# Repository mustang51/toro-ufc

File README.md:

# toro-ufc

USB Up Front Controller, attempting to represent multiple cockpits (F/A-18, F-16, F-15E, A-10C, AV-8B...)

It comprises:

* 12 button numerical pad.
* 10 button in both left and right vertical pads.
* 7 button in horizontal pad.
* 2 rotary encoders with push.
* 2 big buttons.
* 2 small buttons.
* 4 rockers (up/down).
* 2 triple position lever-switches, one with safety cover.
* 4 way dobber lever.
* 6 analog axis (4 lateral, 2 frontal).

## Pin assignments and key matrix

[Pin assignments](doc/pin_assignments.md)

## Bill of materials

* Around 400 grams of PLA for 3D printing.

* 1 STM32F103C6T6 microcontroller.

* 4 ordered PCBs.

* 31 cherry mx switches.

* 2 KY-040 rotary encoders.

* 6 regular 100k potentiometers.

* 12 microswitches.

* 2 MTS-103 ON-OFF-ON lever switches.

* 2 19 mm momentary pushbuttons.

* 12 JST XH 6 pin male PCB connectors.

* 4 JST XH 10 pin male PCB connectors.

* 2 JST XH 8 pin male PCB connectors.

* 1 JST XH 4 pin male PCB connector.

* 44 SMD 0805 diodes.

* 1 JST XH 6 pin 10 mm dual headed cable.

* 1 JST XH 6 pin 20 mm dual headed cable.

* 1 JST XH 8 pin 10 mm dual headed cable.

* 1 JST XH 10 pin 10 mm dual headed cable.

* 8 JST XH 6 pin 20 mm single headed cable.

* 2 JST XJ 10 pin 20 mm single headed cable.

* 1 JST XH 4 pin 20 mm single headed cable.

* 1 mini-USB breakout board.

## Progress pictures

First releases.

Front panel.

Keyswitches PCBs mounted.

First versions of keycaps.

Detail of some PCBs.

[Video of working first prototype.](https://photos.app.goo.gl/QciC3gtiZSFWSCfe9)

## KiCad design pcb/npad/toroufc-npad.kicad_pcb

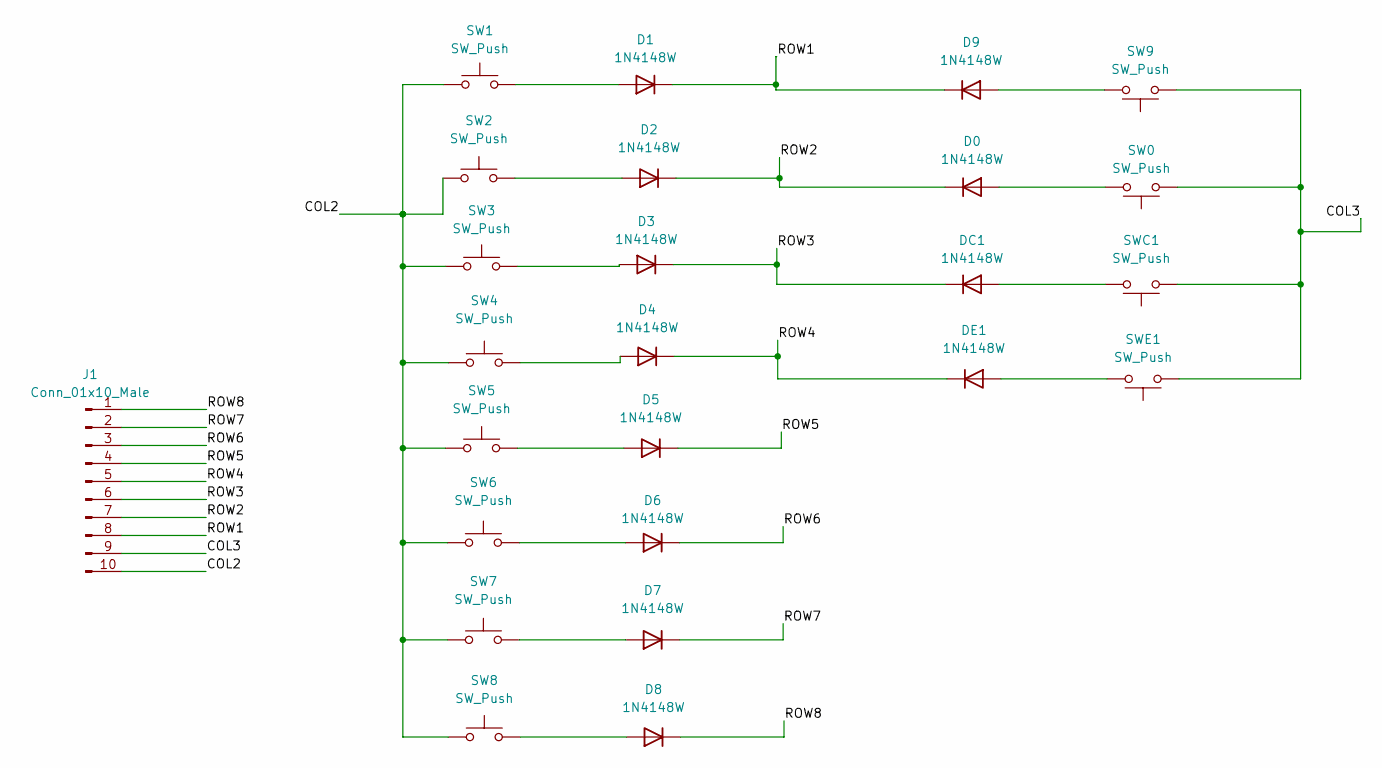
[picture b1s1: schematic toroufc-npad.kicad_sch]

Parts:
D0, D1, D2, D3, D4, D5, D6, D7, D8, D9: 1N4148W; D_SOD-123
DC1: 1N4148W; D_SOD-123
DE1: 1N4148W; D_SOD-123
J1: Conn_01x10_Male; JST_XH_B10B-XH-AM_1x10_P2.50mm_Vertical
SW0, SW1, SW2, SW3, SW4, SW5, SW6, SW7, SW8, SW9: SW_Push; SW_Cherry_MX_PCB
SWC1: SW_Push; SW_Cherry_MX_PCB
SWE1: SW_Push; SW_Cherry_MX_PCB

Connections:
/COL2: J1.10, SW1.1, SW2.1, SW3.1, SW4.1, SW5.1, SW6.1, SW7.1, SW8.1
/COL3: J1.9, SW0.1, SW9.1, SWC1.1, SWE1.1
/ROW1: D1.1 (K), D9.1 (K), J1.8
/ROW2: D0.1 (K), D2.1 (K), J1.7
/ROW3: D3.1 (K), DC1.1 (K), J1.6
/ROW4: D4.1 (K), DE1.1 (K), J1.5
/ROW5: D5.1 (K), J1.4
/ROW6: D6.1 (K), J1.3
/ROW7: D7.1 (K), J1.2
/ROW8: D8.1 (K), J1.1
unnamed: D0.2 (A), SW0.2
unnamed: D1.2 (A), SW1.2
unnamed: D2.2 (A), SW2.2
unnamed: D3.2 (A), SW3.2
unnamed: D4.2 (A), SW4.2
unnamed: D5.2 (A), SW5.2
unnamed: D6.2 (A), SW6.2
unnamed: D7.2 (A), SW7.2
unnamed: D8.2 (A), SW8.2
unnamed: D9.2 (A), SW9.2
unnamed: DC1.2 (A), SWC1.2
unnamed: DE1.2 (A), SWE1.2

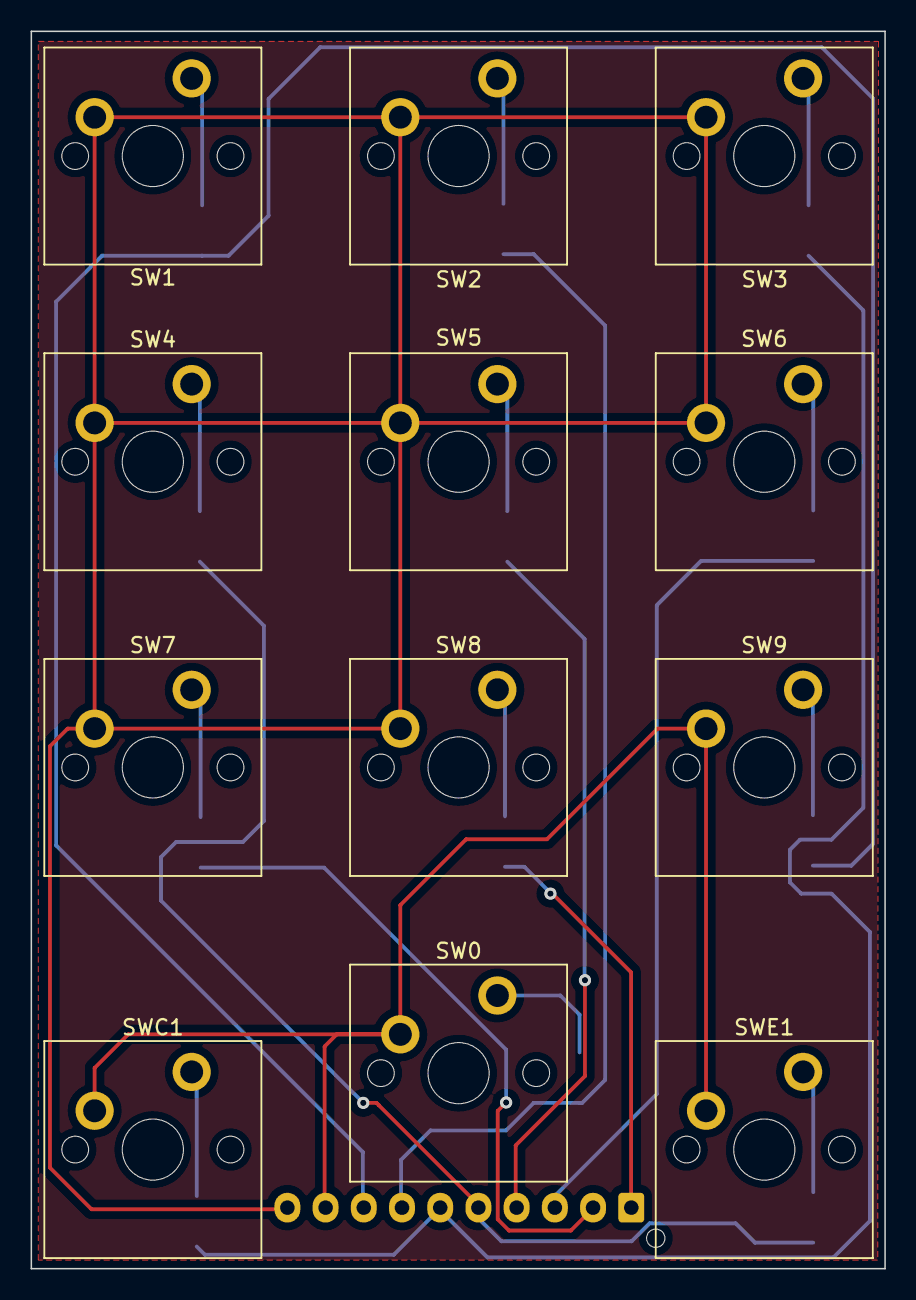
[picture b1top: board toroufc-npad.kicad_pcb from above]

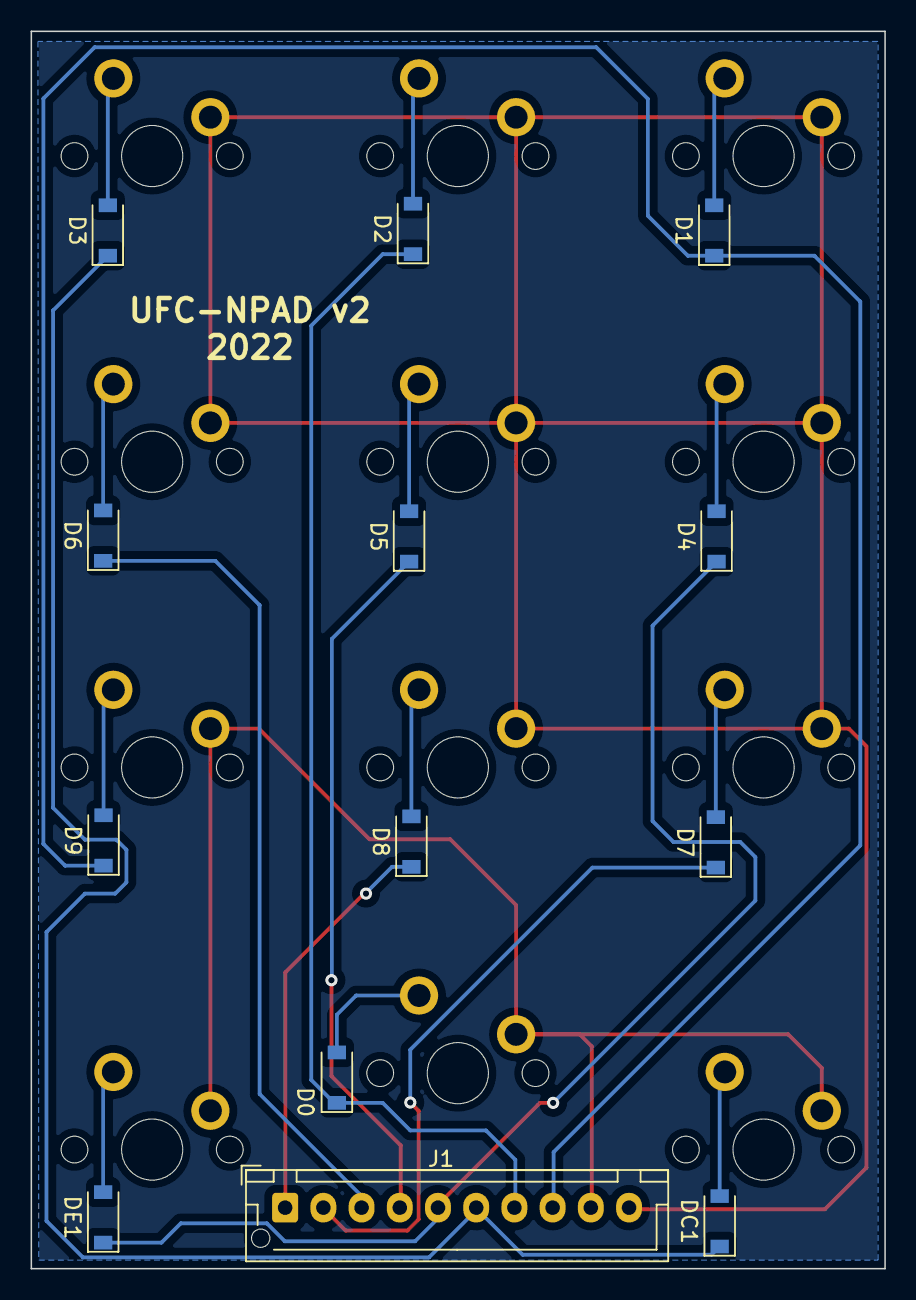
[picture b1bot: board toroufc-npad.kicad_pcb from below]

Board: 2 copper layers, 55.9 x 80.9 mm, 25 parts (13 on the bottom side), 22 nets.

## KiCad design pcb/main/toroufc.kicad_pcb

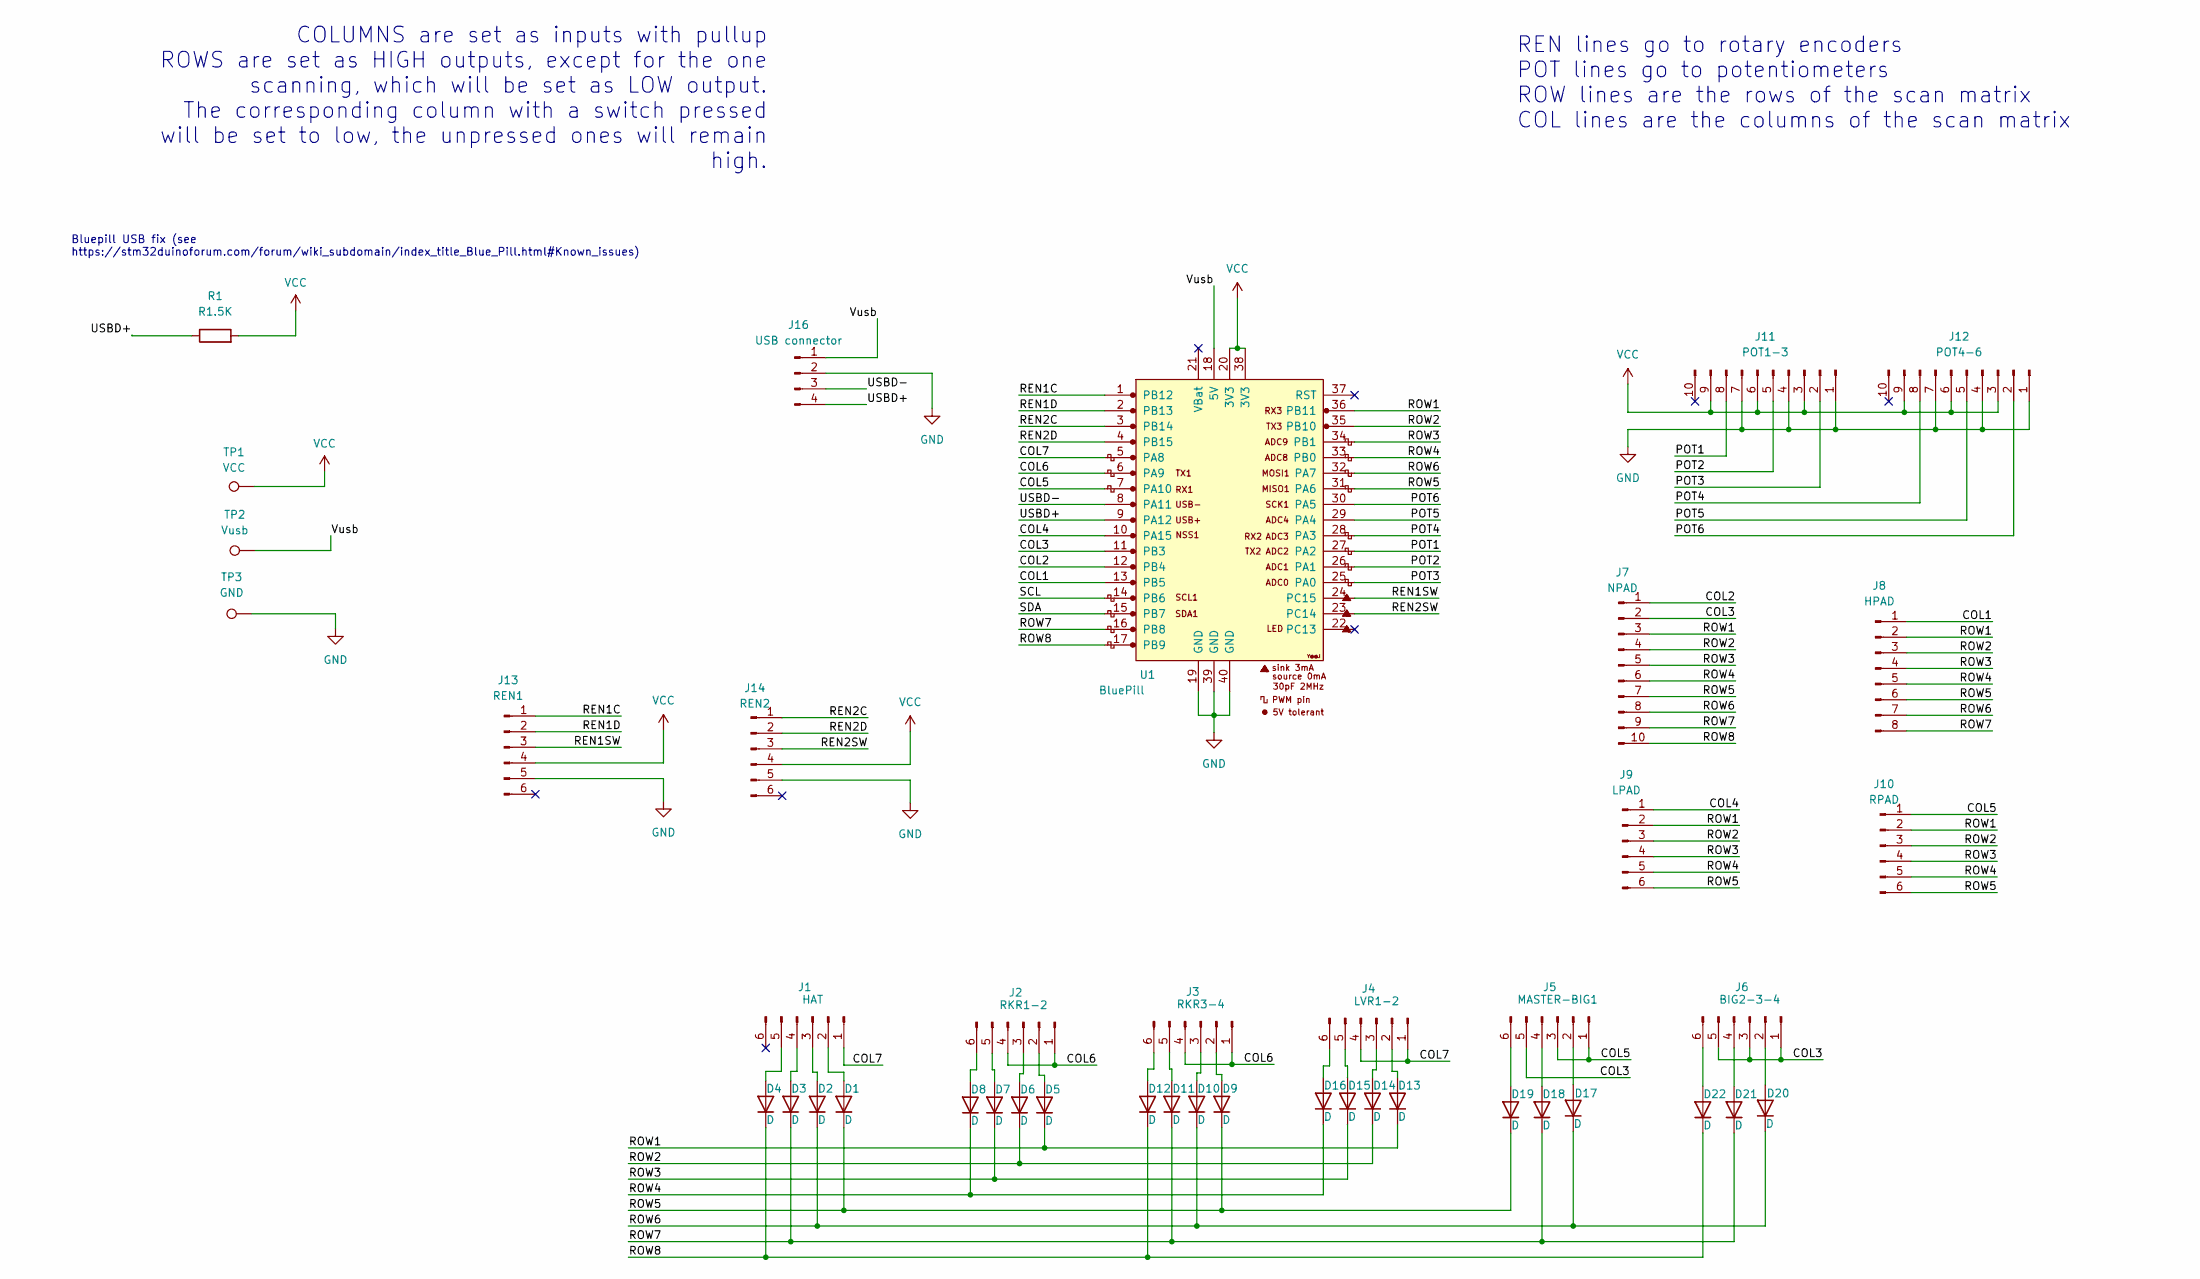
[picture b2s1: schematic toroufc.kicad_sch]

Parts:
D1, D2, D3, D4, D5, D6, D7, D8, D9, D10, D11, D12, D13, D14, D15, D16, D17, D18, D19, D20, D21, D22: D; D_SOD-123
J1: HAT; JST_XH_B6B-XH-A_1x06_P2.50mm_Vertical
J2: RKR1-2; JST_XH_B6B-XH-A_1x06_P2.50mm_Vertical
J3: RKR3-4; JST_XH_B6B-XH-A_1x06_P2.50mm_Vertical
J4: LVR1-2; JST_XH_B6B-XH-A_1x06_P2.50mm_Vertical
J5: MASTER-BIG1; JST_XH_B6B-XH-A_1x06_P2.50mm_Vertical
J6: BIG2-3-4; JST_XH_B6B-XH-A_1x06_P2.50mm_Vertical
J7: NPAD; JST_XH_B10B-XH-A_1x10_P2.50mm_Vertical
J8: HPAD; JST_XH_B8B-XH-A_1x08_P2.50mm_Vertical
J9: LPAD; JST_XH_B6B-XH-A_1x06_P2.50mm_Vertical
J10: RPAD; JST_XH_B6B-XH-A_1x06_P2.50mm_Vertical
J11: POT1-3; JST_XH_B10B-XH-A_1x10_P2.50mm_Vertical
J12: POT4-6; JST_XH_B10B-XH-A_1x10_P2.50mm_Vertical
J13: REN1; JST_XH_B6B-XH-A_1x06_P2.50mm_Vertical
J14: REN2; JST_XH_B6B-XH-A_1x06_P2.50mm_Vertical
J16: USB connector; JST_XH_B4B-XH-A_1x04_P2.50mm_Vertical
R1: R1.5K; R_0805_2012Metric_Pad1.20x1.40mm_HandSolder
TP1: VCC; TestPoint_Pad_2.0x2.0mm
TP2: Vusb; TestPoint_Pad_2.0x2.0mm
TP3: GND; TestPoint_Pad_2.0x2.0mm
U1: BluePill; YAAJ_BluePill_1

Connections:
/COL1: J8.1, U1.13 (PB5)
/COL2: J7.1, U1.12 (PB4)
/COL3: J5.5, J6.1, J6.3, J6.5, J7.2, U1.11 (PB3)
/COL4: J9.1, U1.10 (PA15)
/COL5: J5.1, J5.3, J10.1, U1.7 (PA10)
/COL6: J2.1, J2.4, J3.1, J3.4, U1.6 (PA9)
/COL7: J1.1, J4.1, J4.4, U1.5 (PA8)
/POT1: J11.8, U1.27 (PA2)
/POT2: J11.5, U1.26 (PA1)
/POT3: J11.2, U1.25 (PA0)
/POT4: J12.8, U1.28 (PA3)
/POT5: J12.5, U1.29 (PA4)
/POT6: J12.2, U1.30 (PA5)
/REN1C: J13.1, U1.1 (PB12)
/REN1D: J13.2, U1.2 (PB13)
/REN1SW: J13.3, U1.24 (PC15)
/REN2C: J14.1, U1.3 (PB14)
/REN2D: J14.2, U1.4 (PB15)
/REN2SW: J14.3, U1.23 (PC14)
/ROW1: D5.1 (K), D13.1 (K), J7.3, J8.2, J9.2, J10.2, U1.36 (PB11)
/ROW2: D6.1 (K), D14.1 (K), J7.4, J8.3, J9.3, J10.3, U1.35 (PB10)
/ROW3: D7.1 (K), D15.1 (K), J7.5, J8.4, J9.4, J10.4, U1.34 (PB1)
/ROW4: D8.1 (K), D16.1 (K), J7.6, J8.5, J9.5, J10.5, U1.33 (PB0)
/ROW5: D1.1 (K), D9.1 (K), D19.1 (K), J7.7, J8.6, J9.6, J10.6, U1.31 (PA6)
/ROW6: D2.1 (K), D10.1 (K), D17.1 (K), D20.1 (K), J7.8, J8.7, U1.32 (PA7)
/ROW7: D3.1 (K), D11.1 (K), D18.1 (K), D21.1 (K), J7.9, J8.8, U1.16 (PB8)
/ROW8: D4.1 (K), D12.1 (K), D22.1 (K), J7.10, U1.17 (PB9)
/SCL: U1.14 (PB6)
/SDA: U1.15 (PB7)
/USBD+: J16.4, R1.1, U1.9 (PA12)
/USBD-: J16.3, U1.8 (PA11)
/Vusb: J16.1, TP2.1, U1.18 (5V)
GND: J11.1, J11.4, J11.7, J12.1, J12.4, J12.7, J13.5, J14.5, J16.2, TP3.1, U1.19 (GND), U1.39 (GND), U1.40 (GND)
unnamed: D1.2 (A), J1.2
unnamed: D2.2 (A), J1.3
unnamed: D3.2 (A), J1.4
unnamed: D4.2 (A), J1.5
unnamed: D5.2 (A), J2.2
unnamed: D6.2 (A), J2.3
unnamed: D7.2 (A), J2.5
unnamed: D8.2 (A), J2.6
unnamed: D9.2 (A), J3.2
unnamed: D10.2 (A), J3.3
unnamed: D11.2 (A), J3.5
unnamed: D12.2 (A), J3.6
unnamed: D13.2 (A), J4.2
unnamed: D14.2 (A), J4.3
unnamed: D15.2 (A), J4.5
unnamed: D16.2 (A), J4.6
unnamed: D17.2 (A), J5.2
unnamed: D18.2 (A), J5.4
unnamed: D19.2 (A), J5.6
unnamed: D20.2 (A), J6.2
unnamed: D21.2 (A), J6.4
unnamed: D22.2 (A), J6.6
VCC: J11.3, J11.6, J11.9, J12.3, J12.6, J12.9, J13.4, J14.4, R1.2, TP1.1, U1.20 (3V3), U1.38 (3V3)

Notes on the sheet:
REN lines go to rotary encoders POT lines go to potentiometers ROW lines are the rows of the scan matrix COL lines are the columns of the scan matrix
Bluepill USB fix (see https://stm32duinoforum.com/forum/wiki_subdomain/index_title_Blue_Pill.html#Known_issues)
COLUMNS are set as inputs with pullup ROWS are set as HIGH outputs, except for the one scanning, which will be set as LOW output. The corresponding column with a switch pressed will be set to low, the unpressed ones will remain high.

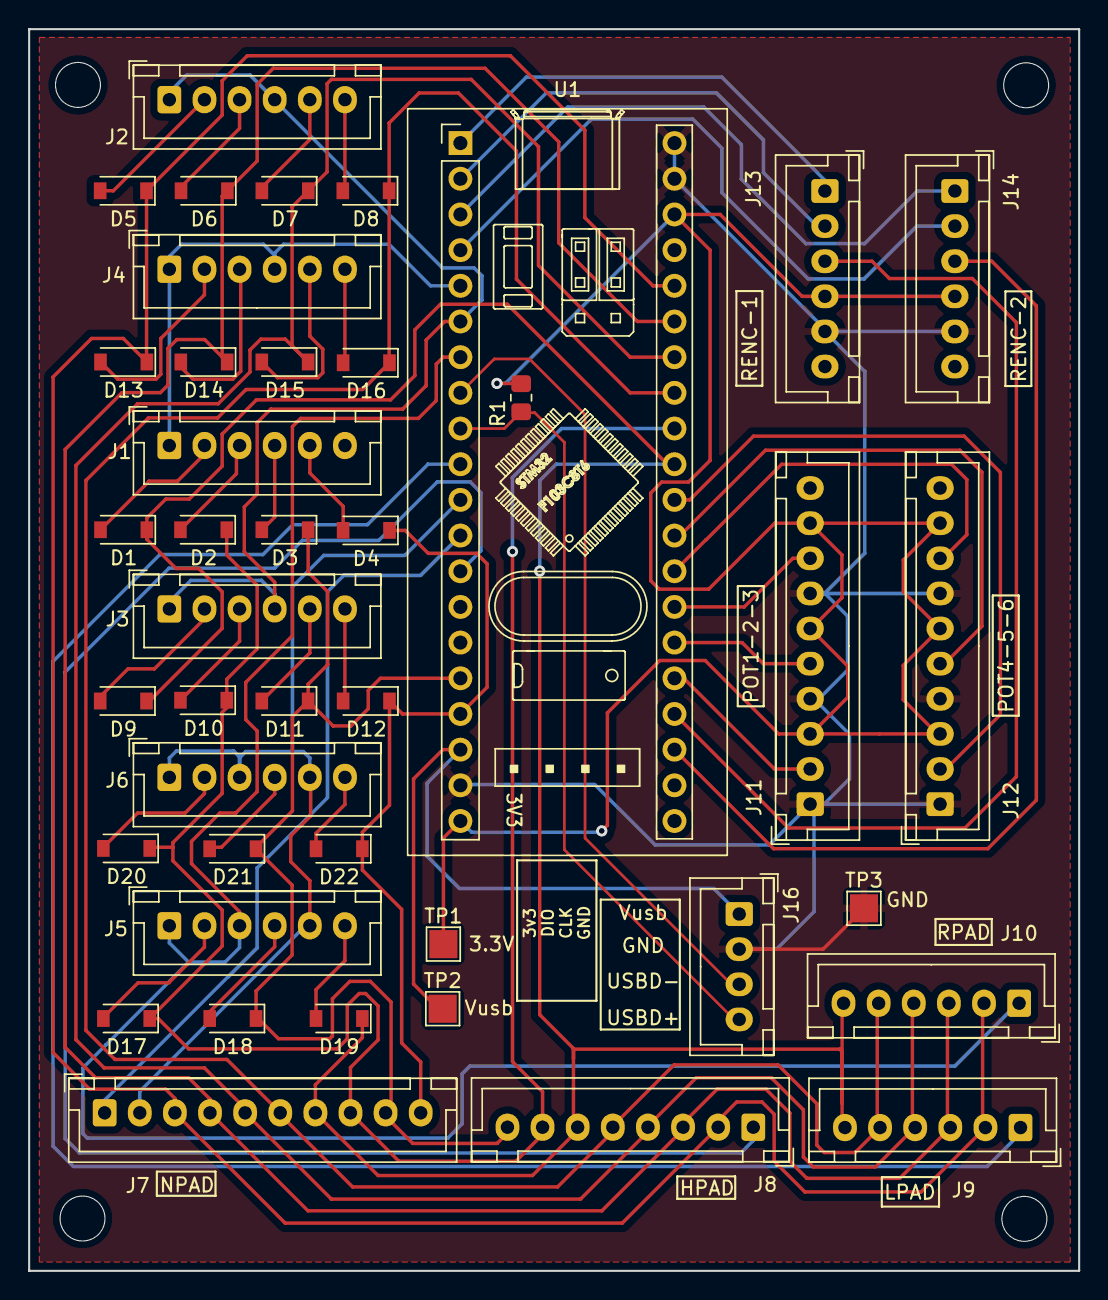
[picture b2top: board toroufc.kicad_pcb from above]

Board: 2 copper layers, 74.8 x 88.4 mm, 42 parts (0 on the bottom side), 54 nets.

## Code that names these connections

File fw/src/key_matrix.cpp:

#include "key_matrix.h"
#include "misc.h"
#include "joystick.h"

#include <Arduino.h>

const unsigned int SCAN_MATRIX_MICROS = 100;
const unsigned int FILTER_AMOUNT = 20;

static uint8_t column_pins[] = {
	PB5, PB4, PB3, PA15, PA10, PA9, PA8
};

static uint8_t columns = sizeof(column_pins);

static uint8_t row_pins[] = {
	PB11, PB10, PB1, PB0, PA6, PA7, PB8, PB9
};

static uint8_t rows = sizeof(row_pins);

static uint8_t key_press[sizeof(column_pins)][sizeof(row_pins)] =
{
	{23, 24, 25, 26, 27, 28, 29,  0},
	{ 1,  2,  3,  4,  5,  6,  7,  8},
	{ 9, 10, 11, 12, 53, 55, 57, 59},
	{13, 14, 15, 16, 17,  0,  0,  0},
	{18, 19, 20, 21, 22, 61, 62,  0},
	{30, 32, 33, 35, 36, 38, 39, 41},
	{47, 49, 50, 52, 42, 43, 44, 45},
};

static uint8_t key_release[sizeof(column_pins)][sizeof(row_pins)] =
{
	{ 0,  0,  0,  0,  0,  0,  0,  0},
	{ 0,  0,  0,  0,  0,  0,  0,  0},
	{ 0,  0,  0,  0, 54, 56, 58, 60},
	{ 0,  0,  0,  0,  0,  0,  0,  0},
	{ 0,  0,  0,  0,  0,  0,  0,  0},
	{ 0,  0,  0,  0,  0,  0,  0,  0},
	{ 0,  0,  0,  0,  0,  0,  0,  0},
};

static uint8_t key_triple[][3] =
{
	{30, 32, 31},
	{33, 35, 34},
	{36, 38, 37},
	{39, 41, 40},
	{47, 49, 48},
	{50, 52, 51},
};

static uint8_t key_fifth[][5] =
{
 	{42, 43, 44, 45, 46},
};

static bool scan_change = false;

static uint8_t triples = sizeof(key_triple) / 3;
static uint8_t fifths = sizeof(key_fifth) / 5;

static bool scan_state[sizeof(column_pins)][sizeof(row_pins)];

static int filter_state[sizeof(column_pins)][sizeof(row_pins)];

static uint8_t scan_row = 0;

bool is_pressed(uint8_t button)
{
	for (uint8_t r = 0; r < columns; r++) {
		for (uint8_t c = 0; c < rows; c++) {
			if (key_press[r][c] != button)
				continue;
			return !scan_state[r][c];
		}
	}
	return false;
}

bool all_triples_off(uint8_t index)
{
	bool ret = true;
	for (unsigned int t = 0; t < 2; t++)
		ret &= !is_pressed(key_triple[index][t]);
	return ret;
}

bool all_fifths_off(uint8_t index)
{
	bool ret = true;
	for (unsigned int t = 0; t < 4; t++)
		ret &= !is_pressed(key_fifth[index][t]);
	return ret;
}

bool filter_position(bool level, uint8_t r, uint8_t c)
{
	if (level == HIGH) {
		if (filter_state[r][c] < 0) {
			filter_state[r][c] = 0;
			return false;
		}

		if (abs(filter_state[r][c]) < FILTER_AMOUNT) {
			filter_state[r][c]++;
			return false;
		}

		return true;

	} else {
		if (filter_state[r][c] > 0) {
			filter_state[r][c] = 0;
			return false;
		}

		if (abs(filter_state[r][c]) < FILTER_AMOUNT) {
			filter_state[r][c]--;
			return false;
		}

		return true;
	}
}

static void scan_position(uint8_t scan_column)
{
	// scan the current column
	bool level = digitalRead(column_pins[scan_column]);

	if (false == filter_position(level, scan_column, scan_row))
		return;

	scan_state[scan_column][scan_row] = level;

	if (LOW == level) { // key pressed
		if (key_release[scan_column][scan_row] != 0) {
			Joystick.setButton(key_release[scan_column][scan_row], false);
			scan_change = true;
		}

		if (key_press[scan_column][scan_row] != 0) {
			Joystick.setButton(key_press[scan_column][scan_row], true);
			scan_change = true;
		}
	} else { // key released
		if (key_press[scan_column][scan_row] != 0) {
			Joystick.setButton(key_press[scan_column][scan_row], false);
			scan_change = true;
		}

		if (key_release[scan_column][scan_row] != 0) {
			Joystick.setButton(key_release[scan_column][scan_row], true);
			scan_change = true;
		}
	}

	return;
}

void scan_triples(void)
{
	if (!scan_change)
		return;

	for (uint8_t t = 0; t < triples; t++) {
		if (all_triples_off(t))
			Joystick.setButton(key_triple[t][2], true);
		else
			Joystick.setButton(key_triple[t][2], false);
	}
}

void scan_fifths(void)
{
	if (!scan_change)
		return;

	for (uint8_t f = 0; f < fifths; f++) {
		if (all_fifths_off(f))
			Joystick.setButton(key_fifth[f][4], true);
		else
			Joystick.setButton(key_fifth[f][4], false);
	}
}

void keymatrix_loop(void)
{
	static unsigned long next_micros = 0;

	if (! time_expired_from(micros(), next_micros))
		return;

	next_micros += SCAN_MATRIX_MICROS;

	for (uint8_t scan_column = 0; scan_column < columns; scan_column++)
		scan_position(scan_column);

	// starting new row, turn off the current one
	digitalWrite(row_pins[scan_row], HIGH);

	scan_row++;
	if (scan_row >= rows) {
                // full matrix scanned.
		scan_row = 0;
		scan_triples();
		scan_fifths();
		scan_change = false;
	}

	// enable the next one and wait for next scan to stabilize
	pinMode(row_pins[scan_row], OUTPUT);
	digitalWrite(row_pins[scan_row], LOW);

	return;
}

void keymatrix_setup()
{
	for (unsigned int r = 0; r < columns; r++) {
		for (unsigned int c = 0; c < rows; c++) {
			filter_state[r][c] = 0;
			scan_state[r][c] = true;
		}
	}

	for (unsigned int r = 0; r < columns; r++)
		pinMode(column_pins[r], INPUT_PULLUP);

	for (unsigned int c = 0; c < rows; c++) {
		pinMode(row_pins[c], OUTPUT);
		digitalWrite(row_pins[c], HIGH);
	}

	// prepare the first row to be scanned
	pinMode(row_pins[0], OUTPUT);
	digitalWrite(row_pins[0], LOW);
}

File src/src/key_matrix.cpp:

#include "key_matrix.h"
#include "misc.h"
#include "joystick.h"

#include <Arduino.h>

const unsigned int SCAN_MATRIX_MICROS = 100;
const unsigned int FILTER_AMOUNT = 20;

static uint8_t row_pins[] = {
	PB1, PB10, PB11, PB9, PB8, PB7
};

static uint8_t rows = sizeof(row_pins);

static uint8_t column_pins[] = {
	PB0, PA5, PA4, PA3, PA2, PA1, PA0
};

static uint8_t columns = sizeof(column_pins);

static uint8_t key_press[sizeof(row_pins)][sizeof(column_pins)] =
{
	{26,  1,  2,  3, 13, 14,  6},
	{ 7, 38, 31, 29, 28,  4,  5},
	{46, 11, 10, 12,  8,  9, 15},
	{44, 34, 40, 43, 37, 17, 16},
 	{32, 41, 42, 39, 35, 18,  0},
	{19, 20, 21, 22, 23, 24, 25},
};

static uint8_t key_release[sizeof(row_pins)][sizeof(column_pins)] =
{
	{0, 0, 0, 0, 0, 0, 0},
	{0, 0, 0, 0, 0, 0, 0},
	{0, 0, 0, 0, 0, 0, 0},
	{0, 0, 0, 0, 0, 0, 0},
	{0, 0, 0, 0, 0, 0, 0},
	{0, 0, 0, 0, 0, 0, 0},
};

static uint8_t key_triple[][3] =
{
 	{26, 28, 27},
 	{29, 31, 30},
 	{32, 34, 33},
 	{35, 37, 36},
 	{44, 46, 45},
};

static uint8_t key_fifth[][5] =
{
 	{40, 41, 42, 43, 57},
};

static bool scan_change = false;

static uint8_t triples = sizeof(key_triple) / 3;
static uint8_t fifths = sizeof(key_fifth) / 5;

static bool scan_state[sizeof(row_pins)][sizeof(column_pins)];

static int filter_state[sizeof(row_pins)][sizeof(column_pins)];

static uint8_t scan_column = 0;

bool is_pressed(uint8_t button)
{
	for (uint8_t r = 0; r < rows; r++) {
		for (uint8_t c = 0; c < columns; c++) {
			if (key_press[r][c] != button)
				continue;
			return !scan_state[r][c];
		}
	}
	return false;
}

bool all_triples_off(uint8_t index)
{
	bool ret = true;
	for (unsigned int t = 0; t < 2; t++)
		ret &= !is_pressed(key_triple[index][t]);
	return ret;
}

bool all_fifths_off(uint8_t index)
{
	bool ret = true;
	for (unsigned int t = 0; t < 4; t++)
		ret &= !is_pressed(key_fifth[index][t]);
	return ret;
}

bool filter_position(bool level, uint8_t r, uint8_t c)
{
	if (level == HIGH) {
		if (filter_state[r][c] < 0) {
			filter_state[r][c] = 0;
			return false;
		}

		if (abs(filter_state[r][c]) < FILTER_AMOUNT) {
			filter_state[r][c]++;
			return false;
		}

		return true;

	} else {
		if (filter_state[r][c] > 0) {
			filter_state[r][c] = 0;
			return false;
		}

		if (abs(filter_state[r][c]) < FILTER_AMOUNT) {
			filter_state[r][c]--;
			return false;
		}

		return true;
	}
}

static void scan_position(uint8_t scan_row)
{
	// scan the current row
	bool level = digitalRead(row_pins[scan_row]);

	if (false == filter_position(level, scan_row, scan_column))
		return;

	scan_state[scan_row][scan_column] = level;

	if (LOW == level) { // key pressed
		if (key_release[scan_row][scan_column] != 0) {
			Joystick.setButton(key_release[scan_row][scan_column], false);
			scan_change = true;
		}

		if (key_press[scan_row][scan_column] != 0) {
			Joystick.setButton(key_press[scan_row][scan_column], true);
			scan_change = true;
		}
	} else { // key released
		if (key_press[scan_row][scan_column] != 0) {
			Joystick.setButton(key_press[scan_row][scan_column], false);
			scan_change = true;
		}

		if (key_release[scan_row][scan_column] != 0) {
			Joystick.setButton(key_release[scan_row][scan_column], true);
			scan_change = true;
		}
	}

	return;
}

void scan_triples(void)
{
	if (!scan_change)
		return;

	for (uint8_t t = 0; t < triples; t++) {
		if (all_triples_off(t))
			Joystick.setButton(key_triple[t][2], true);
		else
			Joystick.setButton(key_triple[t][2], false);
	}
}

void scan_fifths(void)
{
	if (!scan_change)
		return;

	for (uint8_t f = 0; f < fifths; f++) {
		if (all_fifths_off(f))
			Joystick.setButton(key_fifth[f][4], true);
		else
			Joystick.setButton(key_fifth[f][4], false);
	}
}

void keymatrix_loop(void)
{
	static unsigned long next_micros = 0;

	if (! time_expired_from(micros(), next_micros))
		return;

	next_micros += SCAN_MATRIX_MICROS;

	for (uint8_t scan_row = 0; scan_row < rows; scan_row++)
		scan_position(scan_row);

	// starting new column, turn off the current one
	digitalWrite(column_pins[scan_column], HIGH);

	scan_column++;
	if (scan_column >= columns) {
                // full matrix scanned.
		scan_column = 0;
		scan_triples();
		scan_fifths();
		scan_change = false;
	}

	// enable the next one and wait for next scan to stabilize
	pinMode(column_pins[scan_column], OUTPUT);
	digitalWrite(column_pins[scan_column], LOW);

	return;
}

void keymatrix_setup()
{
	for (unsigned int r = 0; r < rows; r++) {
		for (unsigned int c = 0; c < columns; c++) {
			filter_state[r][c] = 0;
			scan_state[r][c] = true;
		}
	}

	for (unsigned int r = 0; r < rows; r++)
		pinMode(row_pins[r], INPUT_PULLUP);

	for (unsigned int c = 0; c < columns; c++) {
		pinMode(column_pins[c], OUTPUT);
		digitalWrite(column_pins[c], HIGH);
	}

	// prepare the first column to be scanned
	pinMode(column_pins[0], OUTPUT);
	digitalWrite(column_pins[0], LOW);
}

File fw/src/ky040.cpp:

#include <Arduino.h>

#include "misc.h"
#include "ky040.h"
#include "joystick.h"

static Rotary rotary0(0, PB13, PB12, PC15, 63 , 64 , 65 , true, true);
static Rotary rotary1(1, PB15, PB14, PC14, 66 , 67 , 68 , true, true);

bool Rotary::push(bool right)
{
	if (right)
		curpos++;
	else
		curpos--;

	uint8_t count = (movement_write - movement_read) % MAX_BUFFER;

	if (count == MAX_BUFFER - 1) { // overflow
		overflow = true;
		return false;
	}

	movements[movement_write] = right;
	movement_write		  = (movement_write + 1) % MAX_BUFFER;

	return true;
}

bool Rotary::pull(bool *right)
{
	if (movement_write == movement_read) // empty
		return false;

	*right        = movements[movement_read];
	movement_read = (movement_read + 1) % MAX_BUFFER;

	return true;
}

Rotary::Rotary(unsigned int index,
	       unsigned int clk, unsigned int data,
	       unsigned int sw,
	       unsigned int button_left, unsigned int button_right,
	       unsigned int button_push,
	       bool half_step, bool no_input_pullups) :
	index(index), clk_pin(clk), data_pin(data),
	sw_pin(sw),
	button_left(button_left), button_right(button_right),
	button_push(button_push),
	half_step(half_step), no_input_pullups(no_input_pullups),
	events(0), overflow(false),
	state(IDLE),
	curpos(0),
	filter_data(0), filter_clk(0), filter_sw(0),
	movement_read(0), movement_write(0)
{
}

void Rotary::setup()
{
	if (no_input_pullups) {
		pinMode(clk_pin, INPUT);
		pinMode(data_pin, INPUT);
	} else {
		pinMode(clk_pin, INPUT_PULLUP);
		pinMode(data_pin, INPUT_PULLUP);
	}

	pinMode(sw_pin, INPUT_PULLUP);

	data = (digitalRead(data_pin) == 1) ? FILTER_AMOUNT : -FILTER_AMOUNT;
	clk = (digitalRead(clk_pin) == 1) ? FILTER_AMOUNT : -FILTER_AMOUNT;
}

bool Rotary::filter_sw_fn(bool level)
{
	if (level == HIGH) {
		if (filter_sw < 0) {
			filter_sw = 0;
			return false;
		}
		if (abs(filter_sw) < FILTER_AMOUNT) {
			filter_sw++;
			return false;
		}
	} else {
		if (filter_sw > 0) {
			filter_sw = 0;
			return false;
		}
		if (abs(filter_sw) < FILTER_AMOUNT) {
			filter_sw--;
			return false;
		}
	}
	return true;
}

void Rotary::poll_sw()
{
	bool state = digitalRead(sw_pin);

	if (false == filter_sw_fn(state))
		return;

	Joystick.setButton(button_push, !state);
}

void Rotary::poll_encoder()
{
	char new_data = digitalRead(data_pin);
	char new_clk = digitalRead(clk_pin);

	if ((new_data == 1) && (filter_data < FILTER_AMOUNT))
		filter_data++;
	if ((new_data == 0) && (-filter_data < FILTER_AMOUNT))
		filter_data--;

	if ((new_clk == 1) && (filter_clk < FILTER_AMOUNT))
		filter_clk++;
	if ((new_clk == 0) && (-filter_clk < FILTER_AMOUNT))
		filter_clk--;

	if ((filter_data != FILTER_AMOUNT) && (filter_data != -FILTER_AMOUNT))
		new_data = data;
	else
		new_data = filter_data;

	if ((filter_clk != FILTER_AMOUNT) && (filter_clk != -FILTER_AMOUNT))
		new_clk = clk;
	else
		new_clk = filter_clk;

	if ((new_data == data) && (new_clk == clk))
		return;

	if (half_step) {
		if (new_data != new_clk) {
			events++;
			if (new_data != data)
				push(false);
			else
				push(true);
		}
	}

	data = new_data;
	clk  = new_clk;
}

void Rotary::poll_machine()
{
	unsigned long now = millis();
	if (state != IDLE) {
		// Button is held left or right, do we have to hold it down a bit?
		if ((now - activity_ms) < TIME_UP)
			return;
	}

	switch(state) {
	case IDLE:
	{
		bool activity;
		bool move_right;

		activity = pull(&move_right);

		if (!activity) {
			if (overflow) {
				overflow = false;
				Joystick.setButton(button_right, false);
				Joystick.setButton(button_left, false);
			}
			return; // no news
		}

		if (move_right) {
			state = RIGHT_PRESSED;
			if (!overflow)
				Joystick.setButton(button_right, true);
		} else {
			state = LEFT_PRESSED;
			if (!overflow)
				Joystick.setButton(button_left, true);
		}
		activity_ms = now;
	}
	break;
	case RIGHT_PRESSED:
		if (!overflow) {
			Joystick.setButton(button_right, false);
		}
		state = IDLE;
		break;
	case LEFT_PRESSED:
		if (!overflow) {
			Joystick.setButton(button_left, false);
		}
		state = IDLE;
		break;
	}

	return;
}

static void rotary_loop_sw(void)
{
	static unsigned long next_millis = 0;
	if (! time_expired_from(millis(), next_millis))
		return;
	next_millis += Rotary::POLL_SW_MS;

	rotary0.poll_sw();
	rotary1.poll_sw();

	return;
}

static void rotary_loop_enc(void)
{
	static unsigned long next_millis = 0;
	if (! time_expired_from(millis(), next_millis))
		return;
	next_millis += Rotary::POLL_ROTARY_MS;

	rotary0.poll_encoder();
	rotary0.poll_machine();

	rotary1.poll_encoder();
	rotary1.poll_machine();

	return;
}

void rotary_setup()
{
	rotary0.setup();
	rotary1.setup();
}

void rotary_loop(void)
{
	rotary_loop_sw();
	rotary_loop_enc();
}

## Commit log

2022-02-06 first
2022-02-06 Starting UFC
2022-02-06 Adding code
2022-02-06 Comments from toro
2022-02-07 Change vendor and product.
2022-02-07 Fix duplicate inline build errors.
2022-02-07 Miscellaneous.
2022-02-07 Mockup image.
2022-02-07 Adding pcb skeleton.
2022-02-07 Mockup image in the readme?
2022-02-07 Shameful description.
2022-02-07 Learning markdown again...
2022-02-07 gitignore
2022-02-07 Moving stuff.
2022-02-07 row->column, column->row
2022-02-07 More
2022-02-07 Connecting, wrong for sure.
2022-02-07 Rinse, repeat.
2022-02-07 More rinsing.
2022-02-07 rinse.
2022-02-07 Reorganizing fw / sw
2022-02-07 Create LICENSE
2022-02-08 Pin assignments rework.
2022-02-08 More work on pin assignments.
2022-02-08 Pin assignments.
2022-02-08 Learning md...
2022-02-08 More tidying up.
2022-02-08 Test
    Test
2022-02-08 Extra file removed.
2022-02-08 Limpiando
2022-02-08 Starting with the PCB.
2022-02-09 First PCB that passes DRC
2022-02-09 Main PCB looking good.
2022-02-09 Syntax
2022-02-09 More.
2022-02-09 Adding 3d models to pcb
2022-02-09 Add mounting holes to pcb.
2022-02-10 Changing pcb connectors to JST XH
2022-02-11 Fixing some lanes.
2022-02-11 Unneeded
2022-02-11 Adding directories for five pcbs.
2022-02-11 Added LPAD pcb.
2022-02-11 Unneeded.
2022-02-11 Missing model paths.
2022-02-12 First RPAD
2022-02-12 Minor fixes
2022-02-12 Added test points, reduced size, removed i2c, labels, bluepill fix.
2022-03-01 First production
2022-03-08 Preparing PCBs v2
2022-05-04 Updating 3d model
2022-05-04 SW changes
2022-05-04 Updating to pcbs v2
2022-05-04 Updating docs
2022-05-04 Removing lateral buttons, now they are extra buttons...
2022-05-04 Workarounds->releases
2022-05-04 Adding WIP pictures
2022-05-04 Adding simple BOM and progress.
2022-05-04 More stuff
2022-05-04 Formatting.
2022-05-04 New render.
2022-05-04 3d model.
2022-06-27 First prototype.
2022-06-27 Learning markdown...
2022-09-24 Modifications for second revision.
2022-10-06 Second model seems to be more or less ready.
2022-11-12 4th onward
2022-11-12 Complete picture
